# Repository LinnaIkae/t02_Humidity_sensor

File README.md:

Welcome to the Microcomputers Lab!
==================================

Term: `Summer Term 2018`

Team Members:   

``` 
1 Leevi Karjalainen
```
``` 
2 Martin Kostal
```

Team/Desk Number:
``` 
02
```
  
Function Unit Name:
``` 
Moisture sensor
```

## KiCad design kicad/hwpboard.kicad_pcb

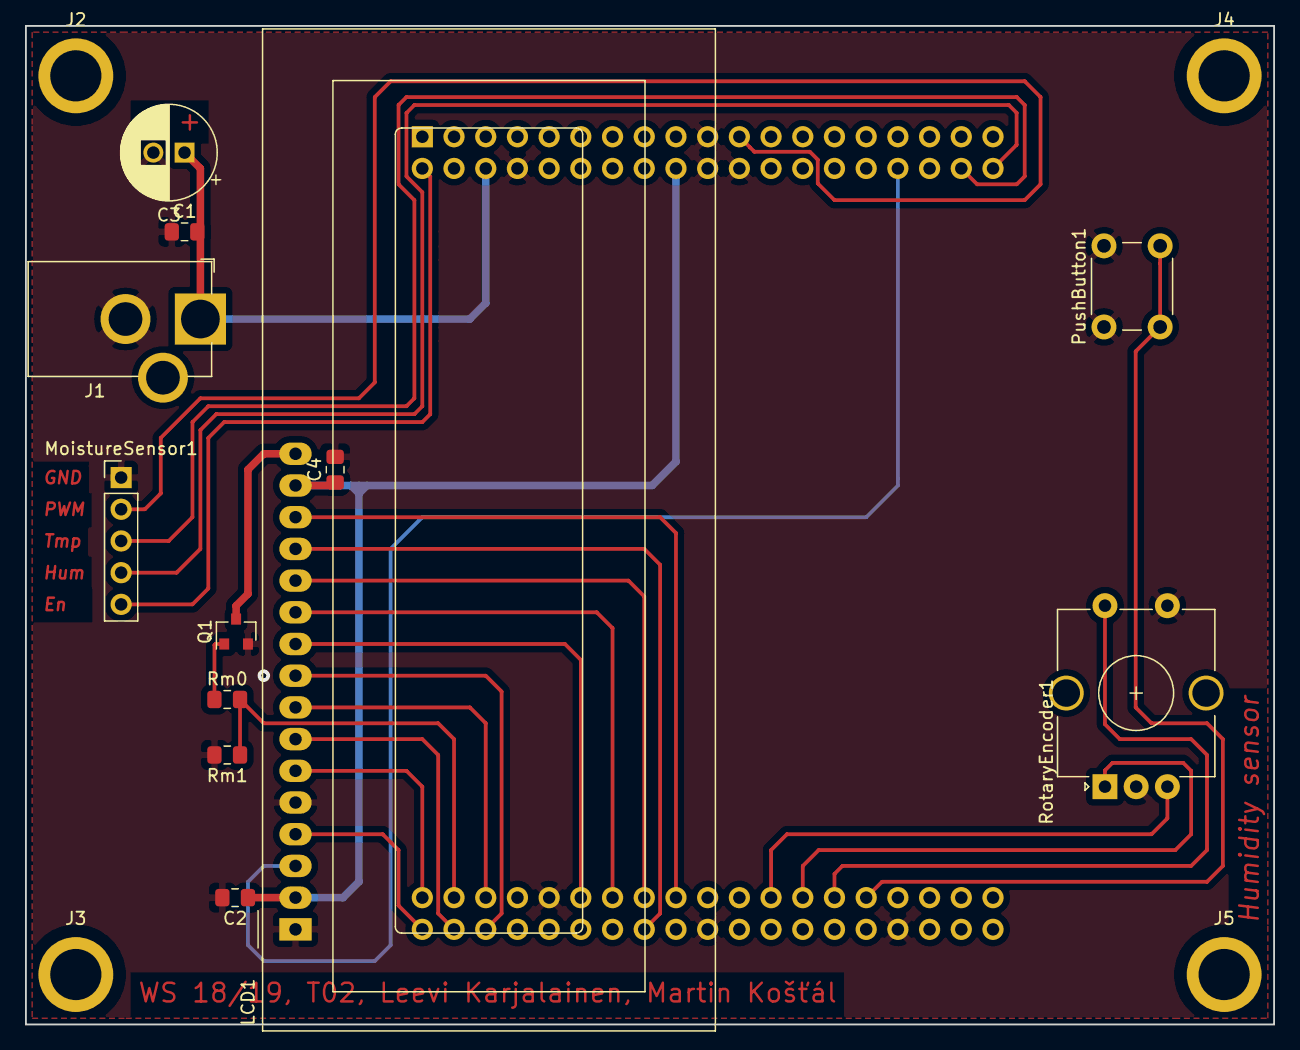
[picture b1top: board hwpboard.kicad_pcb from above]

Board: 2 copper layers, 100.0 x 80.0 mm, 17 parts (1 on the bottom side), 25 nets.

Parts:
C1, C2, C4: 100n; C_0805_2012Metric_Pad1.15x1.40mm_HandSolder
C3: 100u; CP_Radial_D7.5mm_P2.50mm
J1: Barrel_Jack_Switch; BarrelJack_Horizontal_CustomHWP
J2, J3, J4, J5: Conn_01x01; MountingHole_4.1mm_M4_ISO14580_Pad
LCD1: RC1602A; WC1602A_no_mount
MoistureSensor1: Conn_01x05_Male; PinHeader_1x05_P2.54mm_Vertical
NUCBRD1: NUCLEO64; ST_Morpho_Connector_STLink
PushButton1: SW_Push; SW_PUSH_6mm
Q1: BSS138; SOT-23
Rm0: 100; R_0805_2012Metric_Pad1.15x1.40mm_HandSolder
Rm1: 100k; R_0805_2012Metric_Pad1.15x1.40mm_HandSolder
RotaryEncoder1: Rotary_Encoder_Switch; RotaryEncoder_Alps_EC12E-Switch_Vertical_H20mm_CircularMoun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

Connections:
+5V: C2.1, C4.1, LCD1.2, LCD1.15, NUCBRD1.18
DAC0: LCD1.3, NUCBRD1.32
E: LCD1.6, NUCBRD1.39
GND: C1.1, C2.2, C3.2, C4.2, J1.2, LCD1.1, LCD1.5, MoistureSensor1.1, NUCBRD1.8, NUCBRD1.19, NUCBRD1.20, NUCBRD1.22, NUCBRD1.47, NUCBRD1.58, NUCBRD1.70, PushButton1.1, Q1.2, Rm1.2, RotaryEncoder1.C, RotaryEncoder1.S2
unnamed: C1.2, C3.1, J1.1, NUCBRD1.6
unnamed: Q1.1, Rm0.1
PWM_LCD: NUCBRD1.41, Rm0.2, Rm1.1
PWM_sensor: MoistureSensor1.2, NUCBRD1.21
RS: LCD1.4, NUCBRD1.40
Sensor_enable: MoistureSensor1.5, NUCBRD1.2
brightness: LCD1.16, Q1.3
btn0: NUCBRD1.65, RotaryEncoder1.S1
btn1: NUCBRD1.67, PushButton1.2
d0: LCD1.7, NUCBRD1.42
d1: LCD1.8, NUCBRD1.43
d2: LCD1.9, NUCBRD1.44
d3: LCD1.10, NUCBRD1.49
d4: LCD1.11, NUCBRD1.51
d5: LCD1.12, NUCBRD1.53
d6: LCD1.13, NUCBRD1.54
d7: LCD1.14, NUCBRD1.55
humid_out: MoistureSensor1.4, NUCBRD1.38
rotary0: NUCBRD1.63, RotaryEncoder1.A
rotary1: NUCBRD1.61, RotaryEncoder1.B
temp_out: MoistureSensor1.3, NUCBRD1.36

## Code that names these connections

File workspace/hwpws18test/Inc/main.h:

/**
  ******************************************************************************
  * @file           : main.h
  * @brief          : Header for main.c file.
  *                   This file contains the common defines of the application.
  ******************************************************************************
  * This notice applies to any and all portions of this file
  * that are not between comment pairs USER CODE BEGIN and
  * USER CODE END. Other portions of this file, whether 
  * inserted by the user or by software development tools
  * are owned by their respective copyright owners.
  *
  * Copyright (c) 2019 STMicroelectronics International N.V. 
  * All rights reserved.
  *
  * Redistribution and use in source and binary forms, with or without 
  * modification, are permitted, provided that the following conditions are met:
  *
  * 1. Redistribution of source code must retain the above copyright notice, 
  *    this list of conditions and the following disclaimer.
  * 2. Redistributions in binary form must reproduce the above copyright notice,
  *    this list of conditions and the following disclaimer in the documentation
  *    and/or other materials provided with the distribution.
  * 3. Neither the name of STMicroelectronics nor the names of other 
  *    contributors to this software may be used to endorse or promote products 
  *    derived from this software without specific written permission.
  * 4. This software, including modifications and/or derivative works of this 
  *    software, must execute solely and exclusively on microcontroller or
  *    microprocessor devices manufactured by or for STMicroelectronics.
  * 5. Redistribution and use of this software other than as permitted under 
  *    this license is void and will automatically terminate your rights under 
  *    this license. 
  *
  * THIS SOFTWARE IS PROVIDED BY STMICROELECTRONICS AND CONTRIBUTORS "AS IS" 
  * AND ANY EXPRESS, IMPLIED OR STATUTORY WARRANTIES, INCLUDING, BUT NOT 
  * LIMITED TO, THE IMPLIED WARRANTIES OF MERCHANTABILITY, FITNESS FOR A 
  * PARTICULAR PURPOSE AND NON-INFRINGEMENT OF THIRD PARTY INTELLECTUAL PROPERTY
  * RIGHTS ARE DISCLAIMED TO THE FULLEST EXTENT PERMITTED BY LAW. IN NO EVENT 
  * SHALL STMICROELECTRONICS OR CONTRIBUTORS BE LIABLE FOR ANY DIRECT, INDIRECT,
  * INCIDENTAL, SPECIAL, EXEMPLARY, OR CONSEQUENTIAL DAMAGES (INCLUDING, BUT NOT
  * LIMITED TO, PROCUREMENT OF SUBSTITUTE GOODS OR SERVICES; LOSS OF USE, DATA, 
  * OR PROFITS; OR BUSINESS INTERRUPTION) HOWEVER CAUSED AND ON ANY THEORY OF 
  * LIABILITY, WHETHER IN CONTRACT, STRICT LIABILITY, OR TORT (INCLUDING 
  * NEGLIGENCE OR OTHERWISE) ARISING IN ANY WAY OUT OF THE USE OF THIS SOFTWARE,
  * EVEN IF ADVISED OF THE POSSIBILITY OF SUCH DAMAGE.
  *
  ******************************************************************************
  */

/* Define to prevent recursive inclusion -------------------------------------*/
#ifndef __MAIN_H__
#define __MAIN_H__

/* Includes ------------------------------------------------------------------*/

/* USER CODE BEGIN Includes */

/* USER CODE END Includes */

/* Private define ------------------------------------------------------------*/

#define BLUE_BUTTON_Pin GPIO_PIN_13
#define BLUE_BUTTON_GPIO_Port GPIOC
#define BLUE_BUTTON_EXTI_IRQn EXTI15_10_IRQn
#define hum_out_Pin GPIO_PIN_0
#define hum_out_GPIO_Port GPIOC
#define temp_out_Pin GPIO_PIN_1
#define temp_out_GPIO_Port GPIOC
#define USART_TX_Pin GPIO_PIN_2
#define USART_TX_GPIO_Port GPIOA
#define USART_RX_Pin GPIO_PIN_3
#define USART_RX_GPIO_Port GPIOA
#define contrast_Pin GPIO_PIN_4
#define contrast_GPIO_Port GPIOA
#define D3_Pin GPIO_PIN_5
#define D3_GPIO_Port GPIOA
#define D4_Pin GPIO_PIN_6
#define D4_GPIO_Port GPIOA
#define D5_Pin GPIO_PIN_7
#define D5_GPIO_Port GPIOA
#define D2_Pin GPIO_PIN_5
#define D2_GPIO_Port GPIOC
#define rotary_left_Pin GPIO_PIN_10
#define rotary_left_GPIO_Port GPIOB
#define rotary_left_EXTI_IRQn EXTI15_10_IRQn
#define D6_Pin GPIO_PIN_12
#define D6_GPIO_Port GPIOB
#define D0_Pin GPIO_PIN_6
#define D0_GPIO_Port GPIOC
#define RS_Pin GPIO_PIN_8
#define RS_GPIO_Port GPIOC
#define LCD_EN_Pin GPIO_PIN_9
#define LCD_EN_GPIO_Port GPIOC
#define rotaty_right_Pin GPIO_PIN_8
#define rotaty_right_GPIO_Port GPIOA
#define rotaty_right_EXTI_IRQn EXTI9_5_IRQn
#define TMS_Pin GPIO_PIN_13
#define TMS_GPIO_Port GPIOA
#define TCK_Pin GPIO_PIN_14
#define TCK_GPIO_Port GPIOA
#define sensor_enable_Pin GPIO_PIN_11
#define sensor_enable_GPIO_Port GPIOC
#define SWO_Pin GPIO_PIN_3
#define SWO_GPIO_Port GPIOB
#define btn0_Pin GPIO_PIN_4
#define btn0_GPIO_Port GPIOB
#define btn0_EXTI_IRQn EXTI4_IRQn
#define btn1_Pin GPIO_PIN_5
#define btn1_GPIO_Port GPIOB
#define btn1_EXTI_IRQn EXTI9_5_IRQn
#define D7_Pin GPIO_PIN_6
#define D7_GPIO_Port GPIOB
#define PWM_sensor_Pin GPIO_PIN_7
#define PWM_sensor_GPIO_Port GPIOB
#define PWM_brightness_Pin GPIO_PIN_8
#define PWM_brightness_GPIO_Port GPIOB
#define D1_Pin GPIO_PIN_9
#define D1_GPIO_Port GPIOB

/* ########################## Assert Selection ############################## */
/**
  * @brief Uncomment the line below to expanse the "assert_param" macro in the 
  *        HAL drivers code
  */
/* #define USE_FULL_ASSERT    1U */

/* USER CODE BEGIN Private defines */

/* USER CODE END Private defines */

#ifdef __cplusplus
 extern "C" {
#endif
void _Error_Handler(char *, int);

#define Error_Handler() _Error_Handler(__FILE__, __LINE__)
#ifdef __cplusplus
}
#endif

#endif /* __MAIN_H__ */

/************************ (C) COPYRIGHT STMicroelectronics *****END OF FILE****/

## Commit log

2018-10-25 added names and team
2018-10-25 Schematic almost done.
2018-10-25 changes for CubeMX
2018-11-08 schematic v1.0 ready
2018-11-08 layout_all_routed_and_drc_ok_v_1.0
2018-11-12 LCD No Mount
2018-11-14 Many Holes ->1mm
2018-11-15 layout_all_routed_and_drc_ok_beta_2.0
2018-11-22 Board finished and checked
2018-11-22 Gerbers generated
2018-11-22 some edits
2018-11-23 Origin not at right spot
2018-12-06 testing commands, com, dac, interrupt
2018-12-13 Added buttons and debouncing. Also decoded the rotary encoder inputs
2018-12-20 PWMs work now. ADC for humidity also works. Contrast and brightness control work
2019-01-10 LCD screen Hello World works.
2019-01-17 work done
2019-01-24 First version of option menu is working. Bug in hum and temp adc?
2019-01-24 small fixes to LCD, adc:S ARE CONFUSING
2019-01-31 Its working
2019-02-07 adjusted rotary debouncing
